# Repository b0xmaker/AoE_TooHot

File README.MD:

A simple example board showcasing the "It's too hot!" example circuit from Chapter 1 of The Art of Electronics.

BOM through DigiKey: https://www.digikey.com/en/mylists/list/ZIE8KKQNLQ

Schematic:

PCB front:

PCB Rear:

PCB with components:

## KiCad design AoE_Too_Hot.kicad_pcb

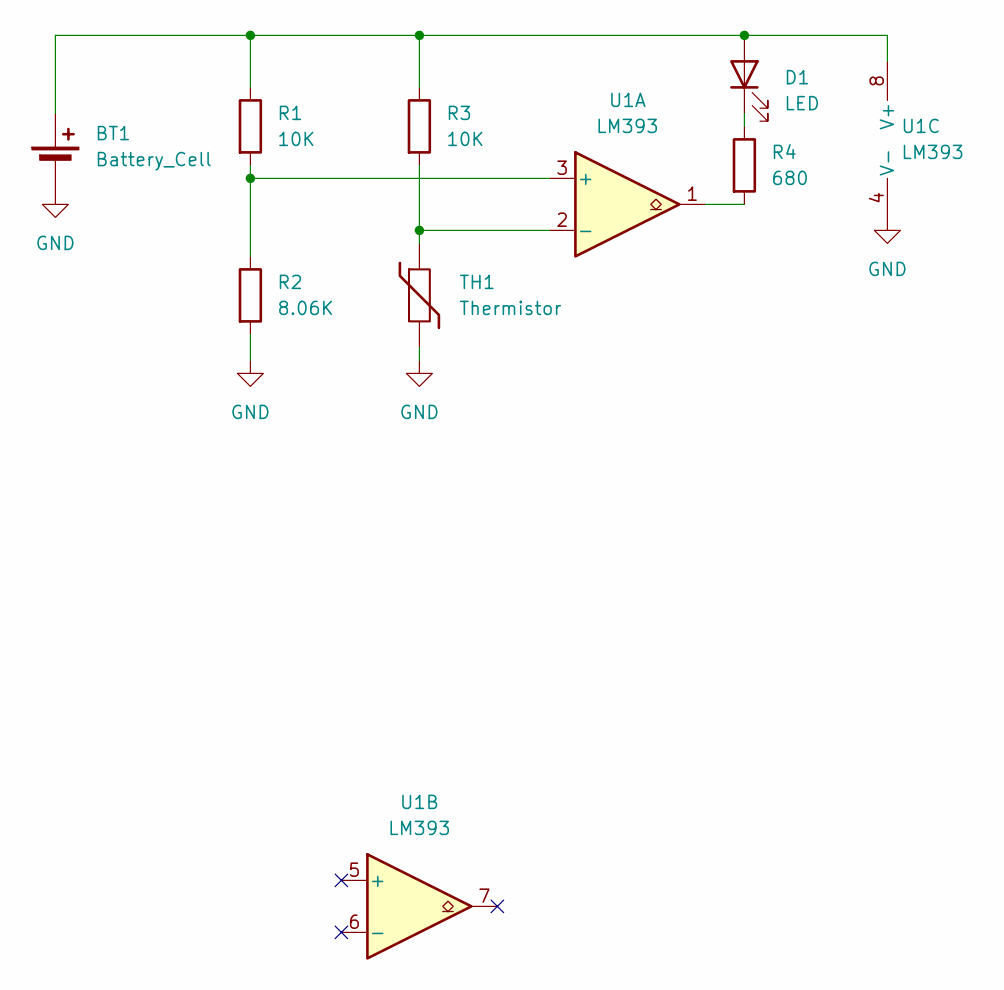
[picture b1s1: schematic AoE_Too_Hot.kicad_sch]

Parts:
BT1: Battery_Cell; BatteryHolder_MPD_BC2003_1x2032
D1: LED; LED_D3.0mm
R1, R3: 10K; R_Axial_DIN0207_L6.3mm_D2.5mm_P10.16mm_Horizontal
R2: 8.06K; R_Axial_DIN0207_L6.3mm_D2.5mm_P10.16mm_Horizontal
R4: 680; R_Axial_DIN0207_L6.3mm_D2.5mm_P10.16mm_Horizontal
TH1: Thermistor; R_Axial_DIN0207_L6.3mm_D2.5mm_P10.16mm_Horizontal
U1: LM393; DIP-8_W7.62mm_LongPads

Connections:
GND: BT1.2 (-), R2.2, TH1.2, U1.4 (V-)
unnamed: BT1.1 (+), D1.2 (A), R1.1, R3.1, U1.8 (V+)
unnamed: D1.1 (K), R4.1
unnamed: R4.2, U1.1
unnamed: R1.2, R2.1, U1.3 (+)
unnamed: R3.2, TH1.1, U1.2 (-)

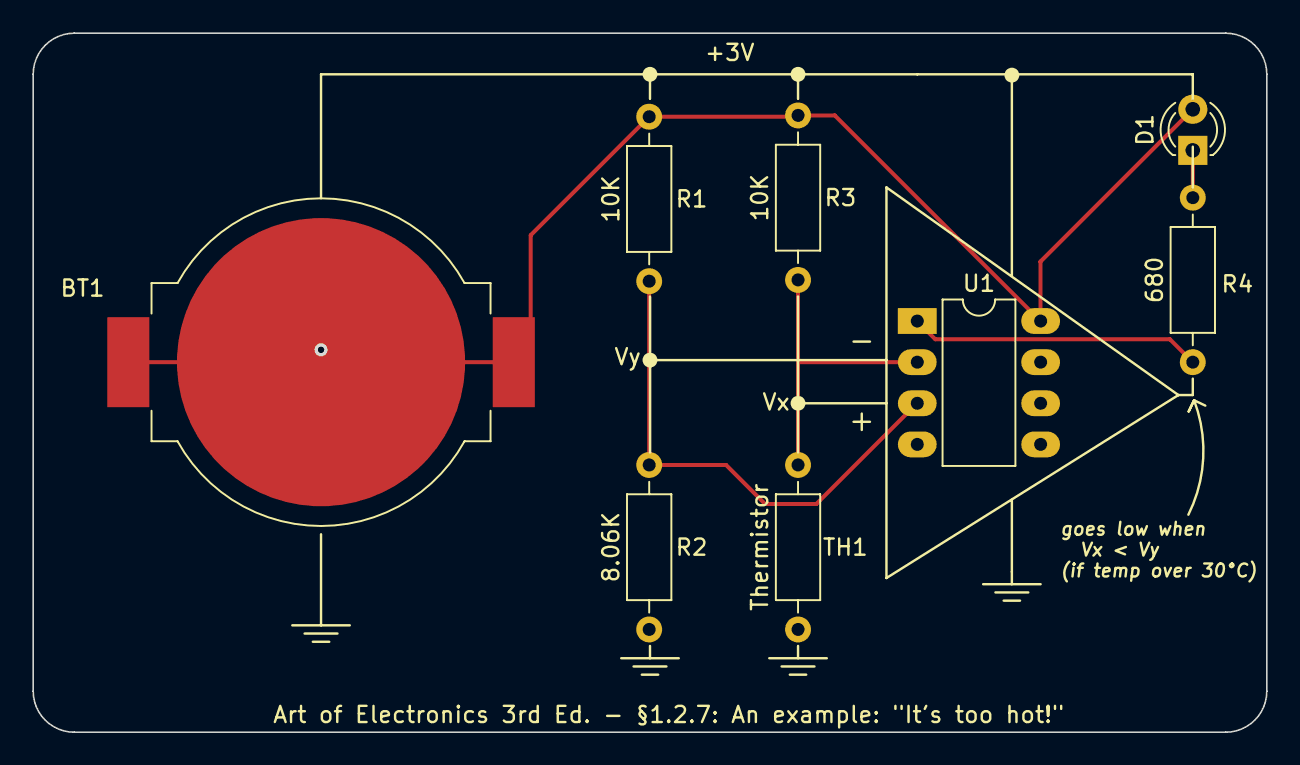
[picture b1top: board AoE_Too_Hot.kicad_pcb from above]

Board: 2 copper layers, 76.2 x 43.2 mm, 8 parts (0 on the bottom side), 6 nets.
